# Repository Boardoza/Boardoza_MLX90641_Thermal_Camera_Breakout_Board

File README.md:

# Boardoza MLX90641 Thermal Camera Breakout Board

The **Boardoza MLX90641 Breakout Board** is a compact and high-performance thermal imaging solution built around the **Melexis MLX90641** far-infrared thermal sensor array. Featuring a **16x12 pixel thermal resolution**, the sensor delivers **192 independent temperature measurement points** for accurate non-contact thermal analysis and object detection applications.

Designed for compatibility with both **3.3V and 5V systems**, the board communicates over a high-speed **I<sup>2</sup>C interface** and supports configurable refresh rates up to **64Hz**. With a wide measurement range from **-40°C to +300°C** and a **55° X axis and 35° Y axis Field of View**, this breakout board is ideal for industrial monitoring, predictive maintenance, thermal mapping, robotics, occupancy sensing, smart appliances, and advanced embedded thermal imaging projects.

## [Click here to purchase!](https://www.ozdisan.com/ureticiler/boardoza)

|Front Side|Back Side|
|:---:|:---:|
| | |

---

## Key Features

- **16x12 Thermal Imaging Array:** Captures 192 individual infrared temperature points for detailed thermal analysis.
- **Wide Temperature Measurement Range:** Measures object temperatures from **-40°C to +300°C** without physical contact.
- **Integrated Thermal Camera Functionality:** Enables compact thermal vision applications without requiring external optics.
- **Fast Refresh Rates:** Adjustable frame rates from **0.5Hz to 64Hz** for dynamic thermal monitoring.
- **Wide Compatibility:** Supports both **3.3V and 5V logic systems** for easy integration with popular development boards.
- **I<sup>2</sup>C Communication:** Supports I<sup>2</sup>C speeds up to **1MHz** for responsive thermal data transfer.
- **Wide Field of View:** Provides a **55° horizontal (X-axis)** and **35° vertical (Y-axis)** viewing angle for broader thermal coverage.  

---

## Technical Specifications

**Model:** MLX90641      
**Manufacturer:** Boardoza   
**Manufacturer IC:** Melexis   
**Functions:** Far-Infrared Thermal Imaging Sensor  
**Thermal Resolution:** 16 x 12 Pixels (192 Pixels)  
**Field of View (FoV):** 55° (X-axis) × 35° (Y-axis)  
**Measurement Range:** -40°C to +300°C  
**Supply Voltage (VCC):** 3.3V to 5.5V DC  
**Logic Voltage Level:** 3.3V / 5V Compatible  
**Communication Interface:** I<sup>2</sup>C  
**I<sup>2</sup>C Clock Frequency:** Up to 1 MHz  
**Sensor Refresh Rate:** 0.5Hz to 64Hz  
**Typical Current Consumption:** ~15mA  
**Operating Temperature:** -40°C to +85°C  
**Board Dimensions:** 20mm x 20mm  

---

## Board Pinout

### ( J1 ) I<sup>2</sup>C Connector

| Pin Number | Pin Name | Description |
|:---:|:---:|---|
| 1 | VCC | Voltage Supply Input |
| 2 | SCL | I<sup>2</sup>C Serial Clock |
| 3 | SDA | I<sup>2</sup>C Serial Data |
| 4 | GND | Ground |

---

## Board Dimensions

---

## Step Files

[Boardoza MLX90641.step](./assets/MLX90641%20Step.step)

---

## Datasheet

[MLX90641 Thermal Sensor Datasheet.pdf](./assets/MLX90641ESF-BCB-000-TU%20Datasheet.pdf)  
[TXS0102 Voltage Level Translator Datasheet.pdf](./assets/TXS0102DCU%20Datasheet.pdf)   
[TLV73333 3.3V LDO Regulator Datasheet.pdf](./assets/TLV73333PDBVR%20Datasheet.pdf)   

---

## Version History

- V1.0.0 - Initial Release

---

## Support

- If you have any questions or need support, please contact support@boardoza.com

---

## **License**

This repository contains both hardware and software components:

### **Hardware Design**

[![CC BY-SA 4.0][cc-by-sa-shield]][cc-by-sa]

All hardware design files are licensed under [Creative Commons Attribution-ShareAlike 4.0 International License][cc-by-sa].

[cc-by-sa]: http://creativecommons.org/licenses/by-sa/4.0/
[cc-by-sa-shield]: https://img.shields.io/badge/License-CC%20BY--SA%204.0-lightgrey.svg

### **Software/Firmware**

[![BSD-3-Clause][bsd-shield]][bsd]

All software and firmware are licensed under [BSD 3-Clause License][bsd].

[bsd]: https://opensource.org/licenses/BSD-3-Clause
[bsd-shield]: https://img.shields.io/badge/License-BSD%203--Clause-blue.svg

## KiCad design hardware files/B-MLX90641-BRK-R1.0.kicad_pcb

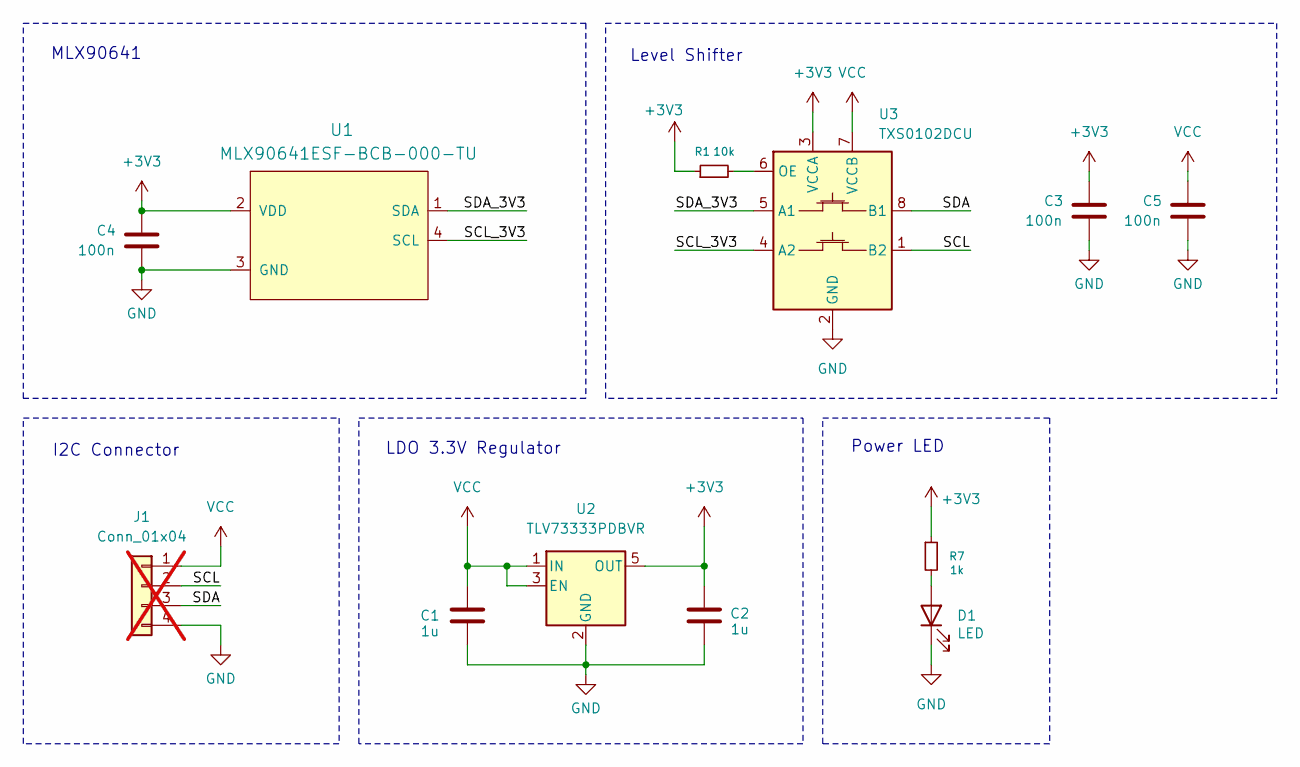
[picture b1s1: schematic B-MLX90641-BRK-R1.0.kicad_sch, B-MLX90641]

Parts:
C1, C2: 1u; C_0603_1608Metric; MANUFACTURER PART CL10A105KO8NNNC
C3, C4, C5: 100n; C_0603_1608Metric; MPN CL10B104KB8WPNC
D1: LED; LED_0603_1608Metric; MANUFACTURER PART LTST-C190KRKT
J1: Conn_01x04; JST_XH_B4B-XH-A_1x04_P2.50mm_Vertical; MPN L-KLS1-2.50-04-SB; not fitted
R1: 10k; R_0603_1608Metric; MANUFACTURER PART 0603SAJ0471T5E
R7: 1k; R_0603_1608Metric; MANUFACTURER PART 0603SAJ0471T5E
U1: MLX90641ESF-BCB-000-TU; MLX90641ESFBCB000TU; MPN MLX90641ESF-BCB-000-TU
U2: TLV73333PDBVR; SOT-23-5; MANUFACTURER PART TLV73333PDBVR
U3: TXS0102DCU; VSSOP-8_2.3x2mm_P0.5mm; MPN TXS0102DCUR

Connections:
+3V3: C2.1, C3.2, C4.2, R1.1, R7.1, U1.2 (VDD), U2.5 (OUT), U3.3 (VCCA)
/SCL: J1.2, U3.1 (B2)
/SCL_3V3: U1.4 (SCL), U3.4 (A2)
/SDA: J1.3, U3.8 (B1)
/SDA_3V3: U1.1 (SDA), U3.5 (A1)
GND: C1.1, C2.2, C3.1, C4.1, C5.1, D1.1 (K), J1.4, U1.3 (GND), U2.2 (GND), U3.2 (GND)
unnamed: D1.2 (A), R7.2
unnamed: R1.2, U3.6 (OE)
VCC: C1.2, C5.2, J1.1, U2.1 (IN), U2.3 (EN), U3.7 (VCCB)

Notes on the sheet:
LDO 3.3V Regulator
MLX90641
Power LED
Level Shifter
I2C Connector

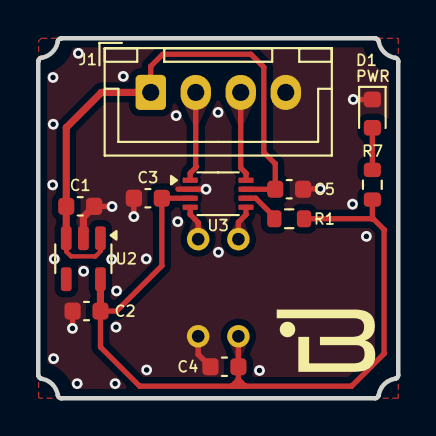
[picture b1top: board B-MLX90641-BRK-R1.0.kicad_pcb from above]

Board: 2 copper layers, 20.0 x 20.0 mm, 12 parts (1 on the bottom side), 9 nets.
